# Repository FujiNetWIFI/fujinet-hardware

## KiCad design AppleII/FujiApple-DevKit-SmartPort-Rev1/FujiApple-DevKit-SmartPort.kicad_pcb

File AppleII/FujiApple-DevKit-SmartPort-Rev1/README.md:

Interactive BOM - https://djtersteegc.github.io/fujinet-hardware/AppleII/ibom-DevKit-SmartPort-v1.0.html

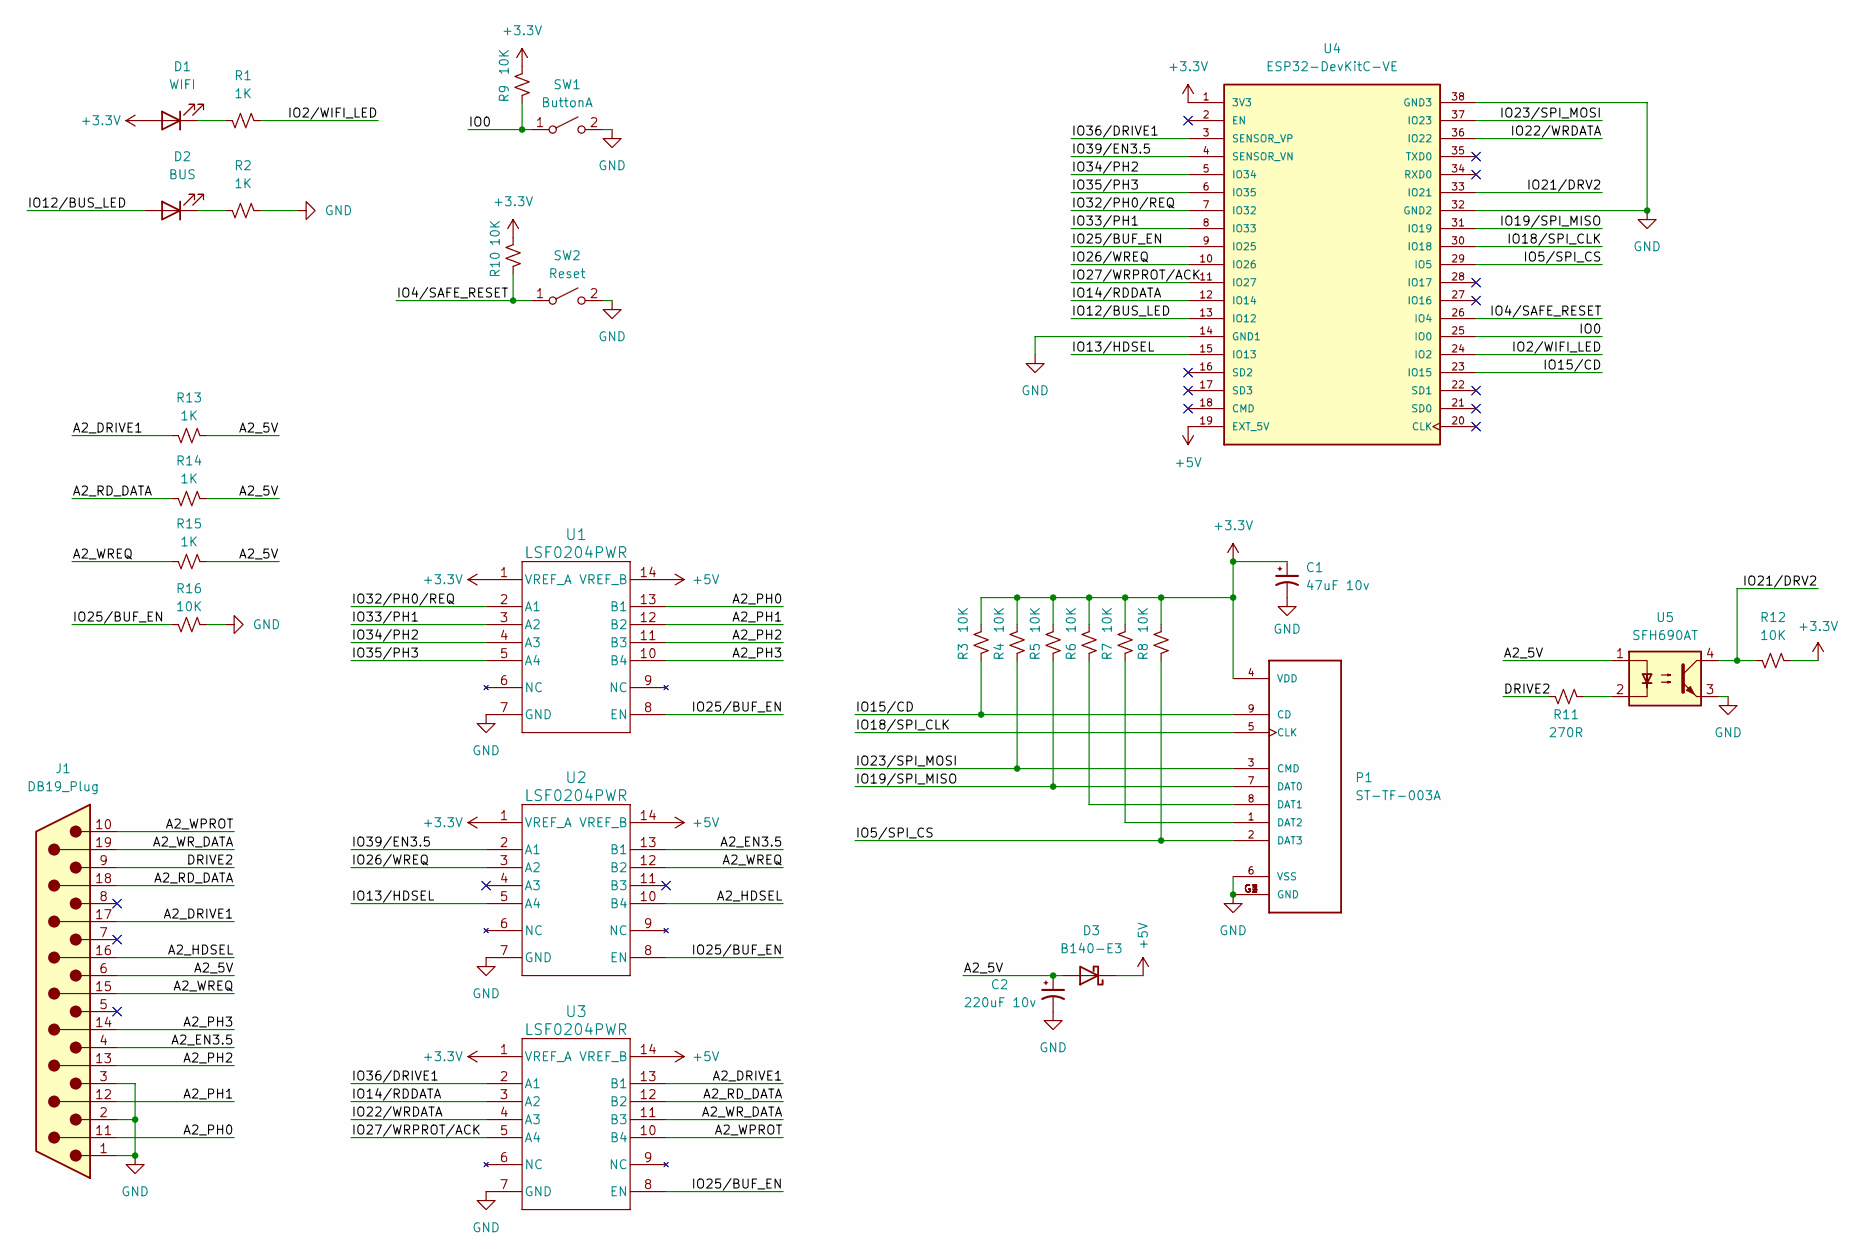
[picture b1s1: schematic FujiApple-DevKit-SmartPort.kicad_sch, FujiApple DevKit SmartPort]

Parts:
C1: 47uF 10v; CP_EIA-3528-15_AVX-H_Pad1.50x2.35mm_HandSolder
C2: 220uF 10v; CP_EIA-7343-30_AVX-N_Pad2.25x2.55mm_HandSolder
D1: WIFI; 1204 Side Emitting LED
D2: BUS; 1204 Side Emitting LED
D3: B140-E3; D_SMA
J1: DB19_Plug; DSUB-19_Male_Vertical_P2.77x2.84mm_Narrow_MountingHoles_Ful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
P1: ST-TF-003A; SUNTECH_ST-TF-003A
R1, R2, R13, R14, R15: 1K; R_0805_2012Metric_Pad1.20x1.40mm_HandSolder
R3, R4, R5, R6, R7, R8, R9, R10, R12, R16: 10K; R_0805_2012Metric_Pad1.20x1.40mm_HandSolder
R11: 270R; R_0805_2012Metric_Pad1.20x1.40mm_HandSolder
SW1: ButtonA; SW_Push_SPST_NO_Alps_SKRK
SW2: Reset; SW_Push_SPST_NO_Alps_SKRK
U1, U2, U3: LSF0204PWR; TSSOP-14_4.4x5mm_P0.65mm
U4: ESP32-DevKitC-VE; MODULE_ESP32-DEVKITC-32U; PARTREV N/A
U5: SFH690AT; SO-4_4.4x3.9mm_P2.54mm

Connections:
+3.3V: C1.1, D1.2 (A), P1.4 (VDD), R3.2, R4.2, R5.2, R6.2, R7.2, R8.2, R9.2, R10.2, R12.2, U1.1 (VREF_A), U2.1 (VREF_A), U3.1 (VREF_A), U4.1 (3V3)
+5V: D3.1 (K), U1.14 (VREF_B), U2.14 (VREF_B), U3.14 (VREF_B), U4.19 (EXT_5V)
/A2_5V: C2.1, D3.2 (A), J1.6, R13.2, R14.2, R15.2, U5.1
/A2_DRIVE1: J1.17, R13.1, U3.13 (B1)
/A2_EN3.5: J1.4, U2.13 (B1)
/A2_HDSEL: J1.16, U2.10 (B4)
/A2_PH0: J1.11, U1.13 (B1)
/A2_PH1: J1.12, U1.12 (B2)
/A2_PH2: J1.13, U1.11 (B3)
/A2_PH3: J1.14, U1.10 (B4)
/A2_RD_DATA: J1.18, R14.1, U3.12 (B2)
/A2_WPROT: J1.10, U3.10 (B4)
/A2_WREQ: J1.15, R15.1, U2.12 (B2)
/A2_WR_DATA: J1.19, U3.11 (B3)
/DRIVE2: J1.9, R11.1
/IO0: R9.1, SW1.1 (A), U4.25 (IO0)
/IO2/WIFI_LED: R1.2, U4.24 (IO2)
/IO4/SAFE_RESET: R10.1, SW2.1 (A), U4.26 (IO4)
/IO5/SPI_CS: P1.2 (DAT3), R8.1, U4.29 (IO5)
/IO12/BUS_LED: D2.2 (A), U4.13 (IO12)
/IO13/HDSEL: U2.5 (A4), U4.15 (IO13)
/IO14/RDDATA: U3.3 (A2), U4.12 (IO14)
/IO15/CD: P1.9 (CD), R3.1, U4.23 (IO15)
/IO18/SPI_CLK: P1.5 (CLK), U4.30 (IO18)
/IO19/SPI_MISO: P1.7 (DAT0), R5.1, U4.31 (IO19)
/IO21/DRV2: R12.1, U4.33 (IO21), U5.4
/IO22/WRDATA: U3.4 (A3), U4.36 (IO22)
/IO23/SPI_MOSI: P1.3 (CMD), R4.1, U4.37 (IO23)
/IO25/BUF_EN: R16.1, U1.8 (EN), U2.8 (EN), U3.8 (EN), U4.9 (IO25)
/IO26/WREQ: U2.3 (A2), U4.10 (IO26)
/IO27/WRPROT/ACK: U3.5 (A4), U4.11 (IO27)
/IO32/PH0/REQ: U1.2 (A1), U4.7 (IO32)
/IO33/PH1: U1.3 (A2), U4.8 (IO33)
/IO34/PH2: U1.4 (A3), U4.5 (IO34)
/IO35/PH3: U1.5 (A4), U4.6 (IO35)
/IO36/DRIVE1: U3.2 (A1), U4.3 (SENSOR_VP)
/IO39/EN3.5: U2.2 (A1), U4.4 (SENSOR_VN)
GND: C1.2, C2.2, J1.1, J1.2, J1.3, P1.6 (VSS), P1.G1 (GND), P1.G2 (GND), P1.G3 (GND), P1.G4 (GND), R2.2, R16.2, SW1.2 (B), SW2.2 (B), U1.7 (GND), U2.7 (GND), U3.7 (GND), U4.14 (GND1), U4.32 (GND2), U4.38 (GND3), U5.3
unnamed: D1.1 (K), R1.1
unnamed: D2.1 (K), R2.1
unnamed: P1.8 (DAT1), R6.1
unnamed: P1.1 (DAT2), R7.1
unnamed: R11.2, U5.2

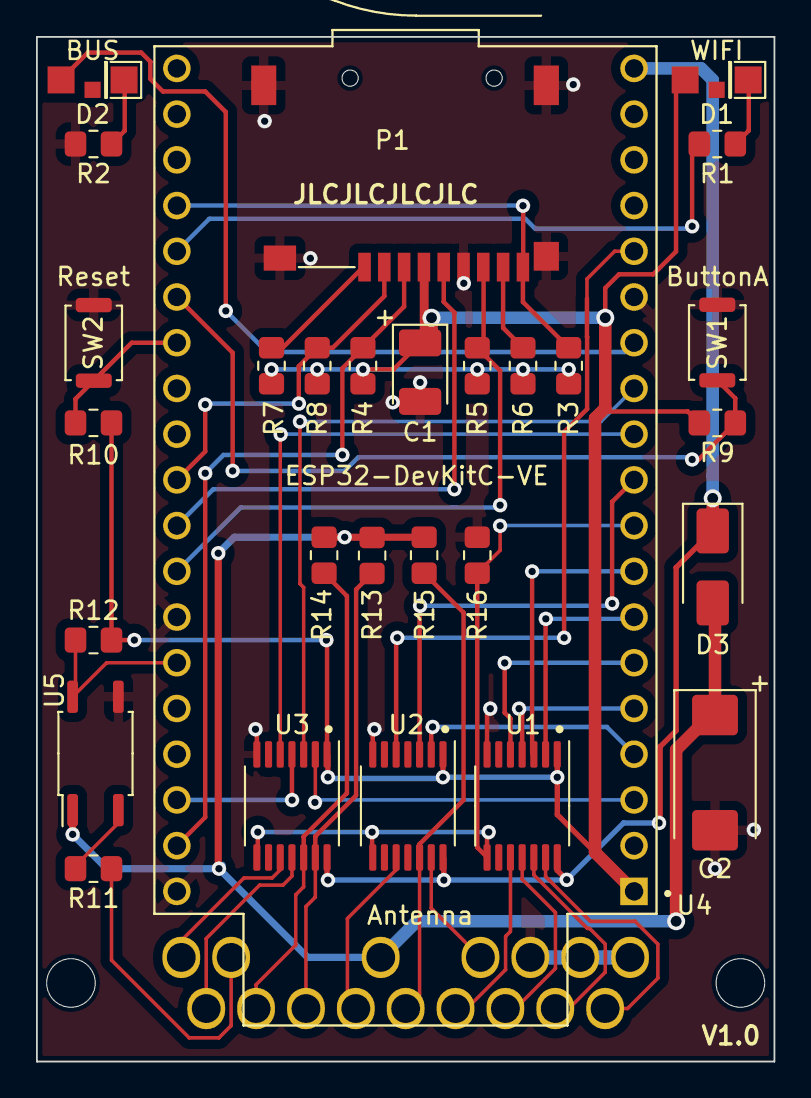
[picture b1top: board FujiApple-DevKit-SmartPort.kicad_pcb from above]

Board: 2 copper layers, 41.0 x 56.9 mm, 30 parts (1 on the bottom side), 43 nets.

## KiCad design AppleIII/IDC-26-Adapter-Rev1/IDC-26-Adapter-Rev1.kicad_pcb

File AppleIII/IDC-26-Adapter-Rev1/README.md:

An IDC-26  to IDC-20 adapter allowing to to use yourApple II Fujinet, Floppy Emu, or Disk II drive on the external floppy port of an Apple III.  Based on the work of [ThorstenBr](https://github.com/ThorstenBr/AppleIII_diskII), but redesigned to plug directly into the external port and adds the option to route the drive 2 enable signal to pin 17, since Fujinet uses a different pin than the Floppy Emu which expects that signal on pin 5.

[Schematic](https://djtersteegc.github.io/fujinet-hardware/AppleIII/Schematic-IDC-26-Adapter-Rev1.pdf)

# BOM

[Interactive BOM](https://djtersteegc.github.io/fujinet-hardware/AppleIII/ibom-Rev1.html)

| Component                          | Qty  | Notes                                 | LCSC                                                         |
| ---------------------------------- | ---- | ------------------------------------- | ------------------------------------------------------------ |
| IDC-20 2.54mm 2x10 Male Box Header | 1    |                                       | [C429961](https://www.lcsc.com/product-detail/IDC-Connectors_JILN-321020SG0ABK00A01_C429961.html) |
| IDC-26 2.54mm 2x13 Female Header   | 1    | Try to find one with a key            | [C2834333](https://www.lcsc.com/product-detail/Female-Headers_TXGA-FFH25407-D26S1004K6K_C2834333.html) |
| 74LS32 SOP or SOIC                 | 1    | SOIC-14_3.9x8.7mm_P1.27mm             | [C521171](https://www.lcsc.com/product-detail/Logic-Gates_XINLUDA-XL74LS32_C521171.html) |
| 470R 0805 Resistor                 | 1    | Only needed for Floppy Emu mode build | [C17710](https://www.lcsc.com/product-detail/Chip-Resistor-Surface-Mount_UNI-ROYAL-Uniroyal-Elec-0805W8F4700T5E_C17710.html) |
| 3.3K 0805 Resistor                 | 3    |                                       | [C26010](https://www.lcsc.com/product-detail/Chip-Resistor-Surface-Mount_UNI-ROYAL-Uniroyal-Elec-0805W8F3301T5E_C26010.html) |
| 100nf 0805 Capacitor               | 1    |                                       | [C28233](https://www.lcsc.com/product-detail/Multilayer-Ceramic-Capacitors-MLCC-SMD-SMT_Samsung-Electro-Mechanics-CL21B104KCFNNNE_C28233.html) |

# Case

The case parts are designed to printed at a 0.2mm layer height and snap together by inserting the wider tab first and then pushing down on the shorter tab side near the 72LS32 chip.  I found the tab on the lid broke off when using matte PLA with it's lower layer bond strength, but regular PLA or PLA+ (and probably PETG) worked fine and could be assembled and disassambled multiple times.  Your mileage may vary.

One issue observed with using a non-keyed female IDC-26 connector is the ability to misalign by one pin inside of the Apple III's IDC-26 male connector when inserting the adpater if you aren't careful. There is a "sleeve" that can be printed to press over the connector to prevent this misalignment from happening.  It's designed as a friction fit based on the generic Chinese connector I was using and a Bambu A1 printing PLA, so tolerances may need to be tweaked for your printer/connector combination.

# Solder Jumpers

**-12V** - Routes -12V to pin 9

**12V** - Routes +12V to pins 13 and 15.  Also pin 17 and 19 depending on their jumper positions.

**PIN5** - Routes either the Drive2 signal or GND to Pin 5.  For use with the Floppy Emu, do NOT also then route Drive2 to Pin17.

**PIN17** - Routes either the Drive 2 signal or +12V to Pin 17. For use with the Fujinet, do NOT also then route Drive2 to Pin5.

**Pin 19** - Routes either the Drive 3 signal or +12V to Pin 19. For use with the Fujinet, experimental, not currently supported in hardware or firmware.

Here's a table of the different ways to can build this and what works.  If you route either Drive2 or Drive3 to pin 17 and 19, you must **NEVER** then attempt to plug an actual Disk II drive into this since they internally bridge +12V on all four pins and will backfeed that voltage into your Apple III drive enable lines.

| Mode       | -12V    | 12V     | Pin 5 | Pin 17 | Pin 19 |
| ---------- | ------- | ------- | ----- | ------ | ------ |
| Disk II    | Closed  | Closed  | GND   | +12V   | +12V   |
| Fujinet    | Open    | Open    | GND   | DRV2   | DRV3   |
| Floppy Emu | Closed* | Closed* | DRV2  | +12V*  | +12V*  |

| Mode       | Disk II                | Fujinet                   | Floppy Emu                |
| ---------- | ---------------------- | ------------------------- | ------------------------- |
| Disk II    | Yes                    | Drive 1 (as .d2) only     | Drive 1 (as .d2) only     |
| Fujinet    | **DANGER, DO NOT USE** | Drive 1 (.d2) and 2 (.d3) | Drive 1 (as .d2) only     |
| Floppy Emu | Yes                    | Drive 1 (as .d2) only     | Drive 1 (.d2) and 2 (.d3) |

*If you don't plan on using a Disk II, I would recommend NOT closing any of the 12V jumpers for safety's sake, since these voltages are not needed by any of these modern drive emulators.

# Assembly

Assemble the SMD components and solder the jumpers as needed.  Note that the 74LS32 chip mounts upside down with pin 1 on the lower right. Then solder on the two IDC connectors, make sure to pay attention to which side of the board they go on.

I like to then add a label printed on a P-touch (0.23mm black on transparent tape) to denote the mode the adapter was built for.

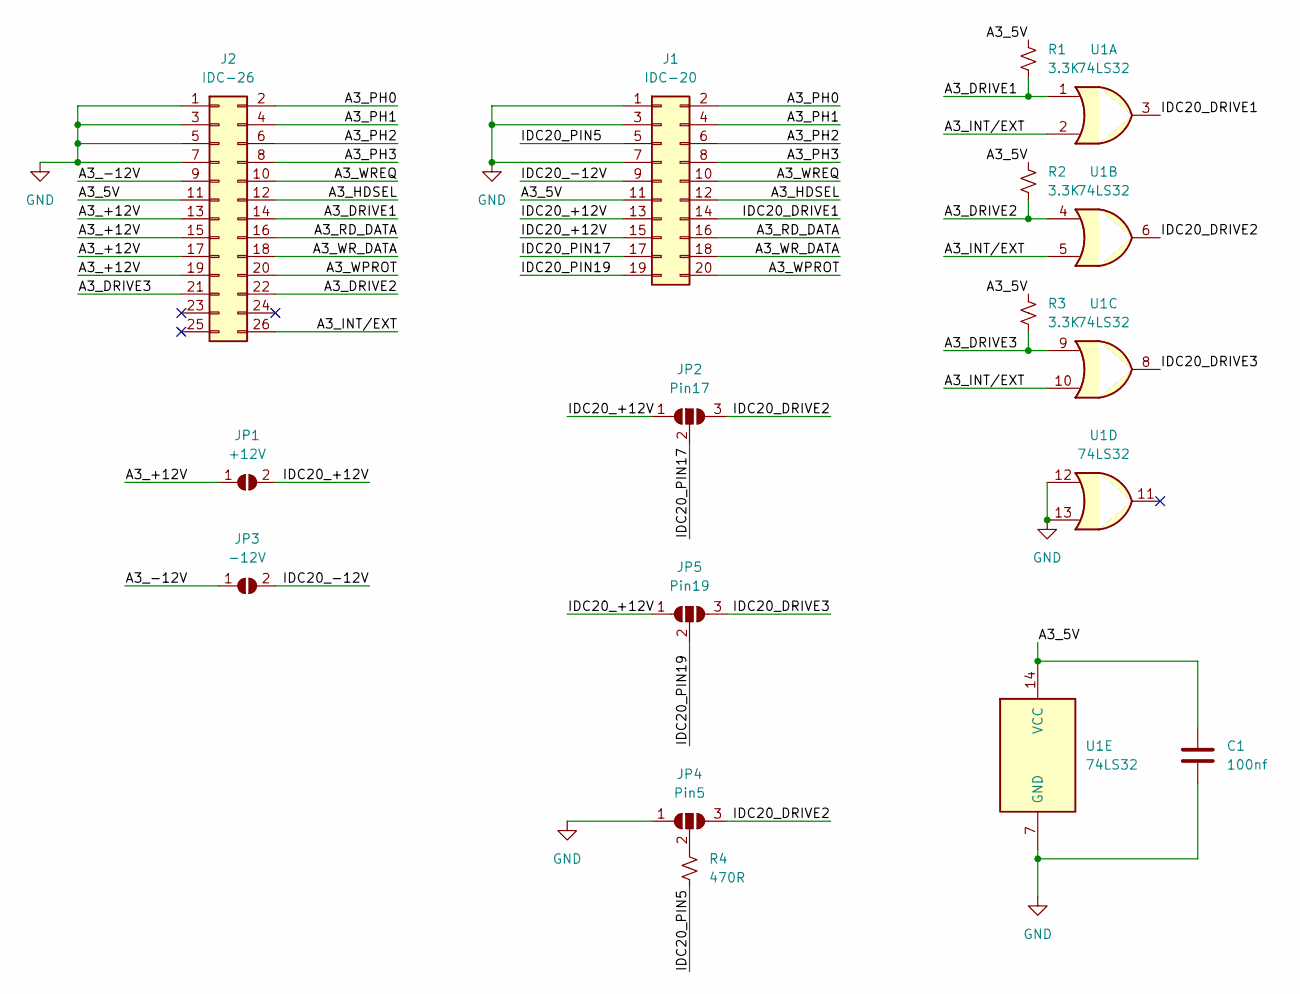
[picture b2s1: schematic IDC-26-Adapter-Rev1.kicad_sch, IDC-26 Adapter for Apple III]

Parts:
C1: 100nf; C_0805_2012Metric_Pad1.18x1.45mm_HandSolder
J1: IDC-20; IDC-Header_2x10_P2.54mm_Vertical
J2: IDC-26; PinSocket_2x13_P2.54mm_Vertical
JP1: +12V; SolderJumper-2_P1.3mm_Open_RoundedPad1.0x1.5mm
JP2: Pin17; SolderJumper-3_P1.3mm_Open_RoundedPad1.0x1.5mm_NumberLabels
JP3: -12V; SolderJumper-2_P1.3mm_Open_RoundedPad1.0x1.5mm
JP4: Pin5; SolderJumper-3_P1.3mm_Open_RoundedPad1.0x1.5mm_NumberLabels
JP5: Pin19; SolderJumper-3_P1.3mm_Open_RoundedPad1.0x1.5mm_NumberLabels
R1, R2, R3: 3.3K; R_0805_2012Metric_Pad1.20x1.40mm_HandSolder
R4: 470R; R_0805_2012Metric_Pad1.20x1.40mm_HandSolder
U1: 74LS32; SOIC-14_3.9x8.7mm_P1.27mm

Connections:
/A3_5V: C1.1, J1.11, J2.11, R1.1, R2.1, R3.1, U1.14 (VCC)
/A3_+12V: J2.13, J2.15, J2.17, J2.19, JP1.1 (A)
/A3_-12V: J2.9, JP3.1 (A)
/A3_DRIVE1: J2.14, R1.2, U1.1
/A3_DRIVE2: J2.22, R2.2, U1.4
/A3_DRIVE3: J2.21, R3.2, U1.9
/A3_HDSEL: J1.12, J2.12
/A3_INT/EXT: J2.26, U1.2, U1.5, U1.10
/A3_PH0: J1.2, J2.2
/A3_PH1: J1.4, J2.4
/A3_PH2: J1.6, J2.6
/A3_PH3: J1.8, J2.8
/A3_RD_DATA: J1.16, J2.16
/A3_WPROT: J1.20, J2.20
/A3_WREQ: J1.10, J2.10
/A3_WR_DATA: J1.18, J2.18
/IDC20_+12V: J1.13, J1.15, JP1.2 (B), JP2.1 (A), JP5.1 (A)
/IDC20_-12V: J1.9, JP3.2 (B)
/IDC20_DRIVE1: J1.14, U1.3
/IDC20_DRIVE2: JP2.3 (B), JP4.3 (B), U1.6
/IDC20_DRIVE3: JP5.3 (B), U1.8
/IDC20_PIN5: J1.5, R4.2
/IDC20_PIN17: J1.17, JP2.2 (C)
/IDC20_PIN19: J1.19, JP5.2 (C)
GND: C1.2, J1.1, J1.3, J1.7, J2.1, J2.3, J2.5, J2.7, JP4.1 (A), U1.7 (GND), U1.12, U1.13
unnamed: JP4.2 (C), R4.1

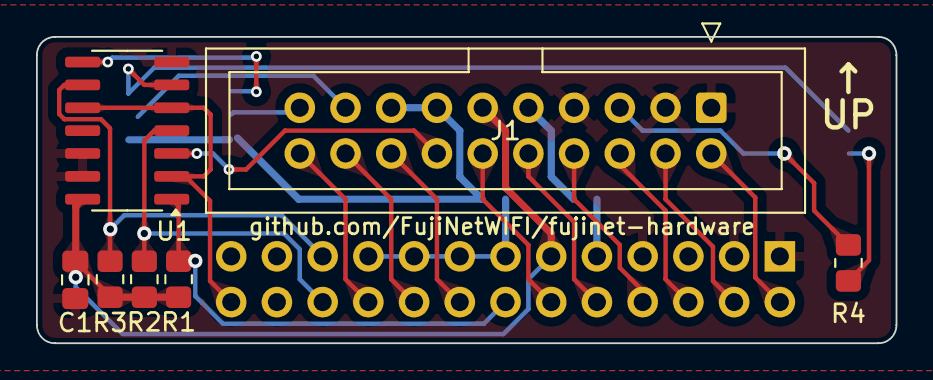
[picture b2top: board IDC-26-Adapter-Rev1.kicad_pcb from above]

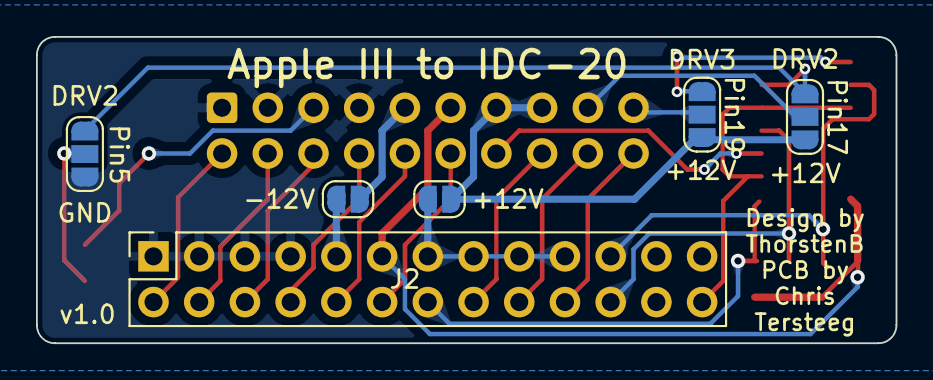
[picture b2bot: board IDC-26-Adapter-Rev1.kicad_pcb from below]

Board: 2 copper layers, 47.8 x 17.0 mm, 13 parts (6 on the bottom side), 26 nets.

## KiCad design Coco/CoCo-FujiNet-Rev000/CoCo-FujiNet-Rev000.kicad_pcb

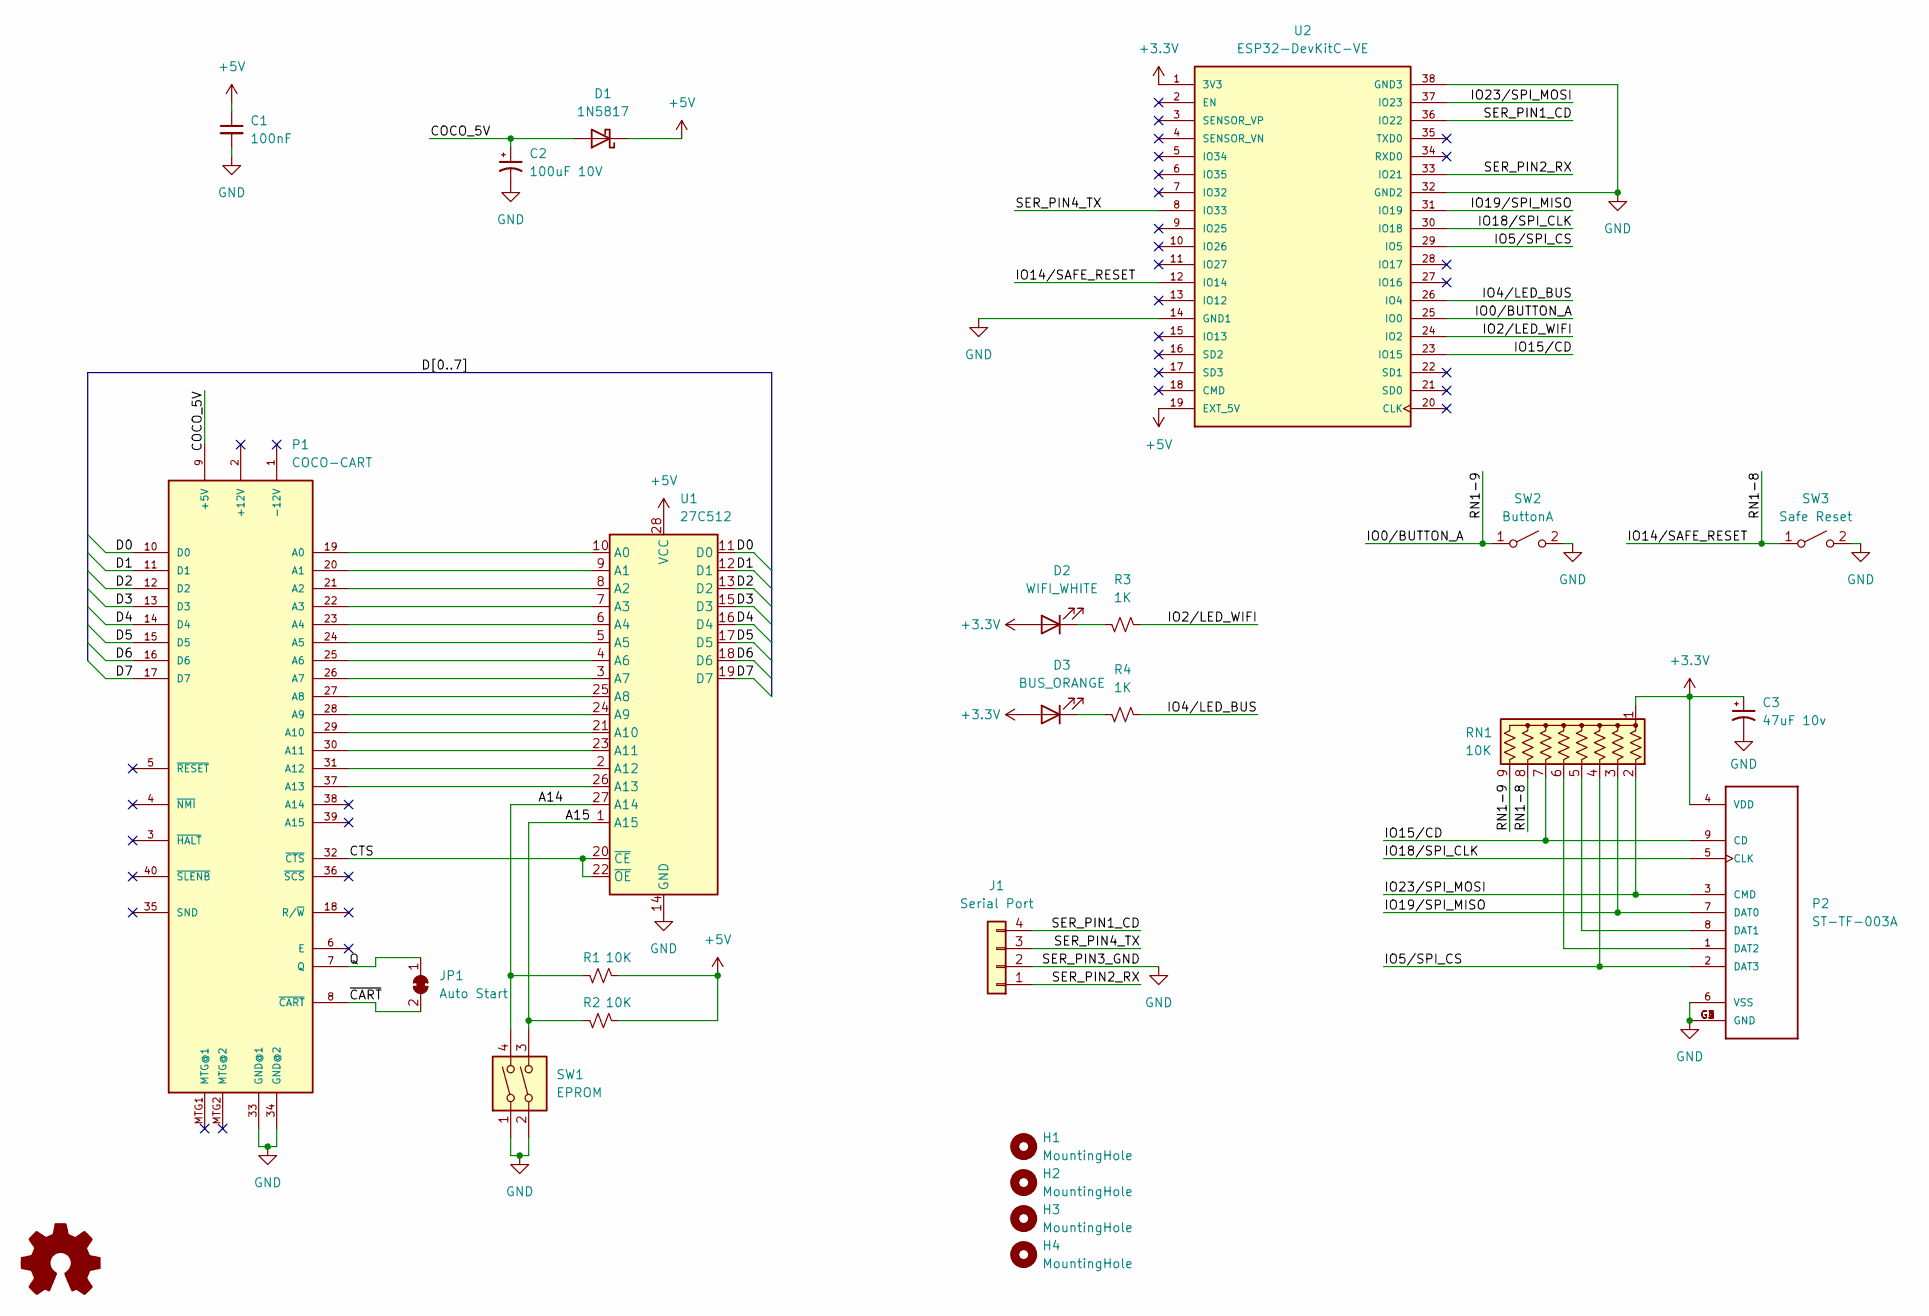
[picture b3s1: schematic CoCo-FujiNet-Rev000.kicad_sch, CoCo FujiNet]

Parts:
C1: 100nF; C_Disc_D4.7mm_W2.5mm_P5.00mm
C2: 100uF 10V; CP_Radial_D6.3mm_P2.50mm
C3: 47uF 10v; CP_EIA-3528-15_AVX-H_Pad1.50x2.35mm_HandSolder
D1: 1N5817; D_DO-41_SOD81_P10.16mm_Horizontal
D2: WIFI_WHITE; LED_D3.0mm
D3: BUS_ORANGE; LED_D3.0mm
H1, H2, H3, H4: MountingHole; MountingHole_3.2mm_M3
J1: Serial Port; PinHeader_1x04_P2.54mm_Vertical
JP1: Auto Start; SolderJumper-2_P1.3mm_Bridged_RoundedPad1.0x1.5mm
P1: COCO-CART
P2: ST-TF-003A; SUNTECH_ST-TF-003A
R1, R2: 10K; R_Axial_DIN0207_L6.3mm_D2.5mm_P7.62mm_Horizontal
R3, R4: 1K; R_Axial_DIN0207_L6.3mm_D2.5mm_P7.62mm_Horizontal
RN1: 10K; R_Array_SIP9
SW1: EPROM; SW_DIP_SPSTx02_Slide_9.78x7.26mm_W7.62mm_P2.54mm
SW2: ButtonA; SW_Tactile_SPST_Angled_PTS645Vx58-2LFS
SW3: Safe Reset; SW_Tactile_SPST_Angled_PTS645Vx58-2LFS
U1: 27C512; DIP-28_W15.24mm
U2: ESP32-DevKitC-VE; MODULE_ESP32-DEVKITC-32U; PARTREV N/A

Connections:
+3.3V: C3.1, D2.2 (A), D3.2 (A), P2.4 (VDD), RN1.1 (common), U2.1 (3V3)
+5V: C1.1, D1.1 (K), R1.2, R2.2, U1.28 (VCC), U2.19 (EXT_5V)
/A14: R1.1, SW1.4, U1.27 (A14)
/A15: R2.1, SW1.3, U1.1 (A15)
/COCO_5V: C2.1, D1.2 (A), P1.9 (+5V)
/CTS: P1.32 (~CTS), U1.20 (~CE), U1.22 (~OE)
/D0: P1.10 (D0), U1.11 (D0)
/D1: P1.11 (D1), U1.12 (D1)
/D2: P1.12 (D2), U1.13 (D2)
/D3: P1.13 (D3), U1.15 (D3)
/D4: P1.14 (D4), U1.16 (D4)
/D5: P1.15 (D5), U1.17 (D5)
/D6: P1.16 (D6), U1.18 (D6)
/D7: P1.17 (D7), U1.19 (D7)
/IO0/BUTTON_A: RN1.9 (R8), SW2.1 (A), U2.25 (IO0)
/IO2/LED_WIFI: R3.2, U2.24 (IO2)
/IO4/LED_BUS: R4.2, U2.26 (IO4)
/IO5/SPI_CS: P2.2 (DAT3), RN1.4 (R3), U2.29 (IO5)
/IO14/SAFE_RESET: RN1.8 (R7), SW3.1 (A), U2.12 (IO14)
/IO15/CD: P2.9 (CD), RN1.7 (R6), U2.23 (IO15)
/IO18/SPI_CLK: P2.5 (CLK), U2.30 (IO18)
/IO19/SPI_MISO: P2.7 (DAT0), RN1.3 (R2), U2.31 (IO19)
/IO23/SPI_MOSI: P2.3 (CMD), RN1.2 (R1), U2.37 (IO23)
/Q: JP1.1 (A), P1.7 (Q)
/SER_PIN1_CD: J1.4, U2.36 (IO22)
/SER_PIN2_RX: J1.1, U2.33 (IO21)
/SER_PIN4_TX: J1.3, U2.8 (IO33)
/~CART: JP1.2 (B), P1.8 (~CART)
GND: C1.2, C2.2, C3.2, J1.2, P1.33 (GND@1), P1.34 (GND@2), P2.6 (VSS), P2.G1 (GND), P2.G2 (GND), P2.G3 (GND), P2.G4 (GND), SW1.1, SW1.2, SW2.2 (B), SW3.2 (B), U1.14 (GND), U2.14 (GND1), U2.32 (GND2), U2.38 (GND3)
unnamed: D2.1 (K), R3.1
unnamed: D3.1 (K), R4.1
unnamed: P1.19 (A0), U1.10 (A0)
unnamed: P1.20 (A1), U1.9 (A1)
unnamed: P1.21 (A2), U1.8 (A2)
unnamed: P1.22 (A3), U1.7 (A3)
unnamed: P1.23 (A4), U1.6 (A4)
unnamed: P1.24 (A5), U1.5 (A5)
unnamed: P1.25 (A6), U1.4 (A6)
unnamed: P1.26 (A7), U1.3 (A7)
unnamed: P1.27 (A8), U1.25 (A8)
unnamed: P1.28 (A9), U1.24 (A9)
unnamed: P1.29 (A10), U1.21 (A10)
unnamed: P1.30 (A11), U1.23 (A11)
unnamed: P1.31 (A12), U1.2 (A12)
unnamed: P1.37 (A13), U1.26 (A13)
unnamed: P2.8 (DAT1), RN1.5 (R4)
unnamed: P2.1 (DAT2), RN1.6 (R5)

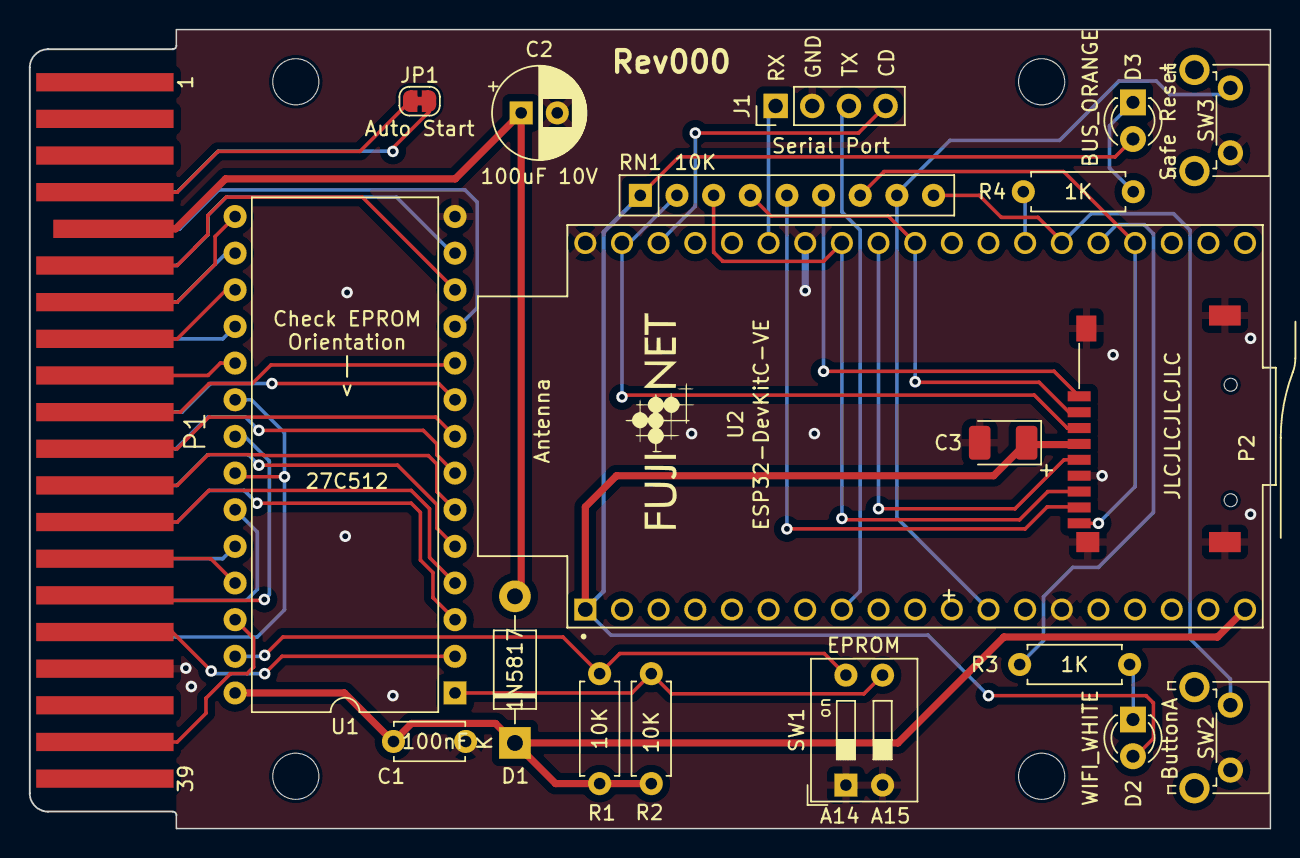
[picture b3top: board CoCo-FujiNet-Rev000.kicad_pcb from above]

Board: 2 copper layers, 86.0 x 55.4 mm, 24 parts (0 on the bottom side), 47 nets.

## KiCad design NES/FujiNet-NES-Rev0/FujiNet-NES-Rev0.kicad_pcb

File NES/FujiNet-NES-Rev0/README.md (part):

# FujiNet-NES Rev0

All-in-one **NES FujiNet cartridge**: one board in a 72-pin Game Pak shell
carrying both halves of the FujiNet stack.

- **RP2354B** (RP2350B die + 2 MB flash, QFN-80, all 48 GPIO used) runs the
  `fujines` cart firmware from `fujinet-firmware/pico/nes` (branch
  `nes-bringup`). It sits on the 5 V cart bus directly through its
  5 V-tolerant pads, serves `$5000-$7FFF` (mailbox, loader ROM, WRAM) and the
  power-on reset vectors itself, watches every CPU write for mapper
  registers, and drives the two SRAMs' bank lines from PIO lookup tables.
- **2x AS6C4008-55** (512K x 8, TSOP-I-32) are the PRG and CHR memories the
  console addresses itself, on the 5 V rail so their outputs drive the 5 V bus.
- **74HCT595 / 253 / 14 / 20 / 00 / 32** on 5 V: the slow control bits, the
  CIRAM A10 mirroring mux, the console-power gate and the SRAM strobe decode.
- **ESP32-S3-WROOM-1-N16R8** runs the **`fujiversal-nes`** build of
  fujinet-firmware and is the USB *host* of the RP (CDC, VID 0xCafe) on
  IO19/IO20; it re-flashes the RP over PICOBOOT.
- **USB-C** (power + CP2102N UART with UMH3N auto-program), **microSD**
  (SPI on IO38-41, card-detect IO42), **WS2812B-2020** status LED,
  RESET / BOOTSEL / S3 EN / S3 BOOT buttons.
- **CIClone** footprint (ATtiny13A, DNP) on the four CIC fingers, so a stock
  NES-001 can run the cart once lockout firmware exists.

**Status (2026-10-01):** schematic audited against the manufacturer
datasheets and redone (`docs/design-review-rev0.md`); 6-layer 1.2 mm layout
generated on the measured NES-EWROM-01 outline -- see *Status* below for
the routing / DRC / export state. **No board has been built**, nothing has
run on a console.

## Edge connector

72 pins, **2.50 mm pitch** (not 0.1 in), pins 1-36 on the label side of the
board, 37-72 on the back, pin N over pin N+36 (nesdev wiki, *Cartridge
connector*). Looking at the label side with the fingers down, the fingers
read **36 .. 1 from left to right: pin 1 is at the right.** The project
footprint `NES_Cart_Edge_72` follows the NES-EWROM-01 board measured on the
nesdev *NES cartridge dimensions* page: fingers 2.0 x 12.0 mm (the four end
fingers 3.0 mm wide at +/-44.25 mm), copper 1.0-13.0 mm in from the bevelled
edge, one solder-mask window per face (the lower 6.5 mm on the label side,
11 mm on the back) exactly as Nintendo's boards have. `tools/check_nets.py`
asserts the orientation from the footprint file and
`tools/audit/edge_orientation.py` compares it with the reference pads.

| Pin | Signal | Net | Pin | Signal | Net |
|---|---|---|---|---|---|
| 1 | GND | GND | 37 | SYSTEM CLK | nc |
| 2-13 | CPU A11..A0 | CA11..CA0 | 38 | M2 | M2 |
| 14 | CPU R/W | RW | 39-41 | CPU A12, A13, A14 | CA12-14 |
| 15 | /IRQ | IRQ_N | 42-49 | CPU D7..D0 | CD7..CD0 |
| 16-20 | EXP0-4 | nc | 50 | /ROMSEL | ROMSEL_N |
| 21 | PPU /RD | PPU_RD_N | 51-55 | EXP9-5 | nc |
| 22 | CIRAM A10 | CIRAM_A10 | 56 | PPU /WR | PPU_WR_N |
| 23-29 | PPU A6..A0 | PA6..PA0 | 57 | CIRAM /CE | CIRAM_CE_N |
| 30-33 | PPU D0-D3 | PD0-3 | 58 | PPU /A13 | PA13_N |
| 34, 35 | CIC toPak, toMB | CIC_TOPAK, CIC_TOMB | 59-61 | PPU A7, A8, A9 | PA7-9 |
| 36 | +5V | CONS_5V | 62, 63 | PPU A11, **A10** | PA11, PA10 |
| | | | 64, 65 | PPU A12, A13 | PA12, PA13 |
| | | | 66-69 | PPU D7..D4 | PD7..PD4 |
| | | | 70, 71 | CIC +RST, CLK | CIC_RST, CIC_CLK |
| | | | 72 | GND | GND |

EXP0-9 and SYSTEM CLK are open. **/IRQ has no pull-up on the cart**: the
console has a 10k pull-up (nesdev), the firmware drives the line low or
releases it.

## RP2354B pin map

Exactly `nes_cart.h`; `tools/check_nets.py` reads the header and checks the
netlist against it (453 checks, including the decode gate by gate).

| GPIO | Net | Goes to |
|---|---|---|
| 0-12 | CA0-CA12 | edge CPU A0-A12 and PRG SRAM A0-A12 |
| 13-20 | CD0-CD7 | edge CPU D0-D7 and PRG SRAM DQ0-7 |
| 21 | M2 | edge 38, the '20 (PRG /WE), test pad |
| 22 | RW | edge 14, '14 and '00 inputs |
| 23 | ROMSEL_N | edge 50, '14 input |
| 24, 25 | CA13, CA14 | edge 40, 41 (PIO1's PRG index) |
| 26-28 | PA10, PA11, PA12 | edge 63, 62, 64 (PIO0's CHR index); PA10/PA11 also '253 1I0/1I1 |
| 29, 30, 31 | SR_SER, SR_SCK, SR_RCK | 74HCT595 DS, SHCP, STCP |
| 32 | IRQ_N | edge 15, direct |
| 33-38 | PRG_A13-PRG_A18 | PRG SRAM A13-A18 (PIO1 table) |
| 39-47 | CHR_A10-CHR_A18 | CHR SRAM A10-A18 (PIO0 table) |

QFN-80 pin numbers were read against the RP2350 datasheet's pinout figure
and KiCad's `MCU_RaspberryPi:RP2354B` symbol; `gen_sch.py` refuses to write
a sheet if `design.py`'s table disagrees with the symbol.

'595 bits, Q0 first: `SRAM_EN`, `PRG_WE_EN`, `CHR_WE_EN`, `MIR0`, `MIR1`,
`FOURSCREEN`, `LED` (1k, green 0603), `SR_SPARE` (test pad). Every bit has a
100k pull-down and the register's **/OE is gated**: outputs float (so the
bits read 0) for ~70-170 ms after the 5 V rail comes up and whenever the
console is off, so the undefined power-on contents of the '595 can never
enable an SRAM before the RP has loaded it.

## Decode

All 74HCT, on the +5V rail. `ROMSEL = !ROMSEL_N`, `RW_N = !RW`.

```
VSENSE        = CONS_5V * 100k/(22k+100k) = 0.82 x CONS_5V   (TI 74HCT14 VT+ reaches 0.70 x VCC)
PWR_OK_N      = !VSENSE          PWR_OK = !PWR_OK_N          both on the '14 (Schmitt)
POR           = !POR_RC          POR_RC: 1 uF to +5V, 100k to GND (starts high, decays)
'595 /OE      = NAND(PWR_OK, POR)
PRG /CE       = NAND(ROMSEL, SRAM_EN)                       '20 (4-input, spare inputs high)
PRG /OE       = NAND(R/W, PWR_OK)                           '00
PRG /WE       = NAND(M2, ROMSEL, RW_N, PRG_WE_EN)            '20: one gate after M2 falls
CHR /CE       = PPU A13
CHR /OE       = PPU /RD | PWR_OK_N                          '32
CHR /WE       = PPU /WR | !CHR_WE_EN                        '32
CIRAM A10     = '253 half a { PPU A10, PPU A11, 0, 1 }[MIR1:MIR0], /OE = PWR_OK_N
CIRAM /CE     = '253 half b ( PPU /A13 | FOURSCREEN ), /OE = PWR_OK_N
```

Gate budget: '14 6 of 6, '20 2 of 2, '00 2 of 4, '32 3 of 4, '253 both
halves; every unused input is grounded. The truth table the firmware sees is
the one in `pico/nes/README.md`; the differences are in *how* the lines are
driven: `CIRAM /CE` tri-states with the console off instead of being a '32
output into a dead console, the PRG write strobe ends on M2 rather than on
the console's /ROMSEL decoder (`tools/audit/timing_margins.py`: 28 ns
worst-case after M2 falls against the 2A03's PROVISIONAL 30 ns data hold;
the first draft was 110 ns), and `FOURSCREEN` is a '595 bit with a pull-down.

### Timing budget (NTSC, nesdev and the AS6C4008-55 datasheet)

| Path | Budget | Spent |
|---|---|---|
| CPU read of PRG SRAM: /ROMSEL low to data valid | 330 ns | '14 + '20 (58 ns worst) + tACE 55 ns = 113 ns |
| CPU write to PRG SRAM (loader copy): data hold after /WE rises | tDH 0 ns | /WE rises <= 28 ns after M2 falls; 2A03 holds ~30 ns (PROVISIONAL) |
| write pulse / data setup | tWP 45 / tDW 25 ns | ~300 ns / ~228 ns |
| PPU fetch: PPU A10-A12 change to CHR data | 372 ns (2 dots) | PIO table ~45 ns + tACE 55 ns; /OE one '32 after /RD |
| Mirroring: PPU A10 to CIRAM A10 | same PPU access | '253 ~20 ns |
| CIRAM /CE from PPU /A13 | same | '32 + '253 ~40 ns |

## Power

- **Sources:** console +5V (edge 36, `CONS_5V`) through an **AO3401A
  P-FET** whose gate is VBUS: with no cable it is fully on (~24 mV at
  0.4 A), with USB present it is off and only its body diode remains,
  pointing into the cart, so USB never back-feeds the console. USB VBUS
  comes in through an SS34. Both meet on **+5V**. R22 (4.7k, VBUS to GND)
  holds the gate at 0 V with no cable: the SS34 is reverse-biased whenever
  the console powers the cart, and its leakage (0.5 mA max at 25 C) would
  otherwise lift the gate through the 69k sense divider alone and turn the
  FET off (added 2026-10-07, after layout; found by the SMS Rev0 audit).
- **+5V** feeds the two SRAMs, the six 74HCT packages (VCC minimum 4.5 V,
  which the Schottky drop of the first draft left no margin for), the
  WS2812B (datasheet VDD 3.7-5.3 V), the AP63203 buck and the AP2112K LDO.
- **+3V3** (AP63203, 2 A, 4 ms soft-start): ESP32-S3, microSD, CP2102N.
- **+3V3_RP** (AP2112K, 20 us start-up, ~60 mA): every RP2354B supply pin:
  IOVDD x8, QSPI_IOVDD, USB_OTP_VDD, ADC_AVDD, and the core-regulator input
  VREG_VIN with VREG_AVDD through 33R (the datasheet asks for those two to
  rise together). The RP2350's pads are 5 V-tolerant *only while IOVDD is
  powered*; on console-only power the buck's soft-start would leave them
  unpowered for ms with the 2A03's outputs already at 5 V. The LDO tracks the
  console rail as it rises instead. (Keeping VREG_VIN on the buck would also
  have left pin 64 boxed in between LX and FB with no via spot at 0.4 mm
  pitch; on the island it joins through a stub under the package.)
- **PWR_OK** is sensed on `CONS_5V`, before the FET, so a USB-powered cart in
  an unpowered console keeps both SRAM /OE high, the '595 off and the '253
  released. Because the SRAMs and logic stay on USB power, a loaded game
  survives a console power cycle while the cable is in.

## Flashing

- **ESP32-S3:** USB-C (CP2102N, esptool auto-program),
  `pio run -e fujiversal-nes -t upload`. The build embeds the RP image.
- **RP2354B:** flashed by the S3 over PICOBOOT at boot -- mailbox BOOTSEL
  doorbell first, else IO5 holds QSPI_SS low across an IO4 pulse on RUN
  (1k links, both 3.3 V, no transistors: `forceBootselViaPins()` drives
  low to assert). `fujiversal-nes.h` does not define `PIN_RP2040_RUN/BOOTSEL`
  yet; the board follows the IO4/IO5 contract and `check_nets.py` says so
  when it falls back to the INTV header.
- **Manual fallback:** hold SW2 (BOOTSEL) and press SW1 (RESET); in BOOTSEL
  the RP enumerates to the S3, not a PC.
- **Last resort:** test pads TP1 SWCLK, TP2 SWDIO, TP3 GND, TP4 RUN.
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
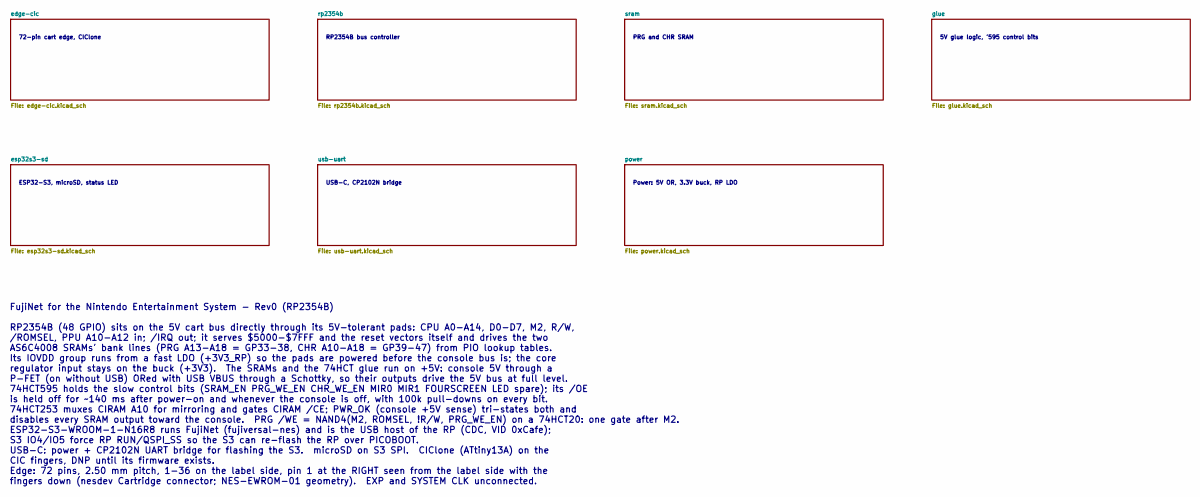
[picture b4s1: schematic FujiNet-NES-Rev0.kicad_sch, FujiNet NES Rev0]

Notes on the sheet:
72-pin cart edge, CIClone
RP2354B bus controller
PRG and CHR SRAM
5V glue logic, '595 control bits
ESP32-S3, microSD, status LED
USB-C, CP2102N bridge
Power: 5V OR, 3.3V buck, RP LDO
FujiNet for the Nintendo Entertainment System - Rev0 (RP2354B) RP2354B (48 GPIO) sits on the 5V cart bus directly through its 5V-tolerant pads: CPU A0-A14, D0-D7, M2, R/W, /ROMSEL, PPU A10-A12 in; /IRQ out; it serves $5000-$7FFF and the reset vectors itself and drives the two AS6C4008 SRAMs' bank l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

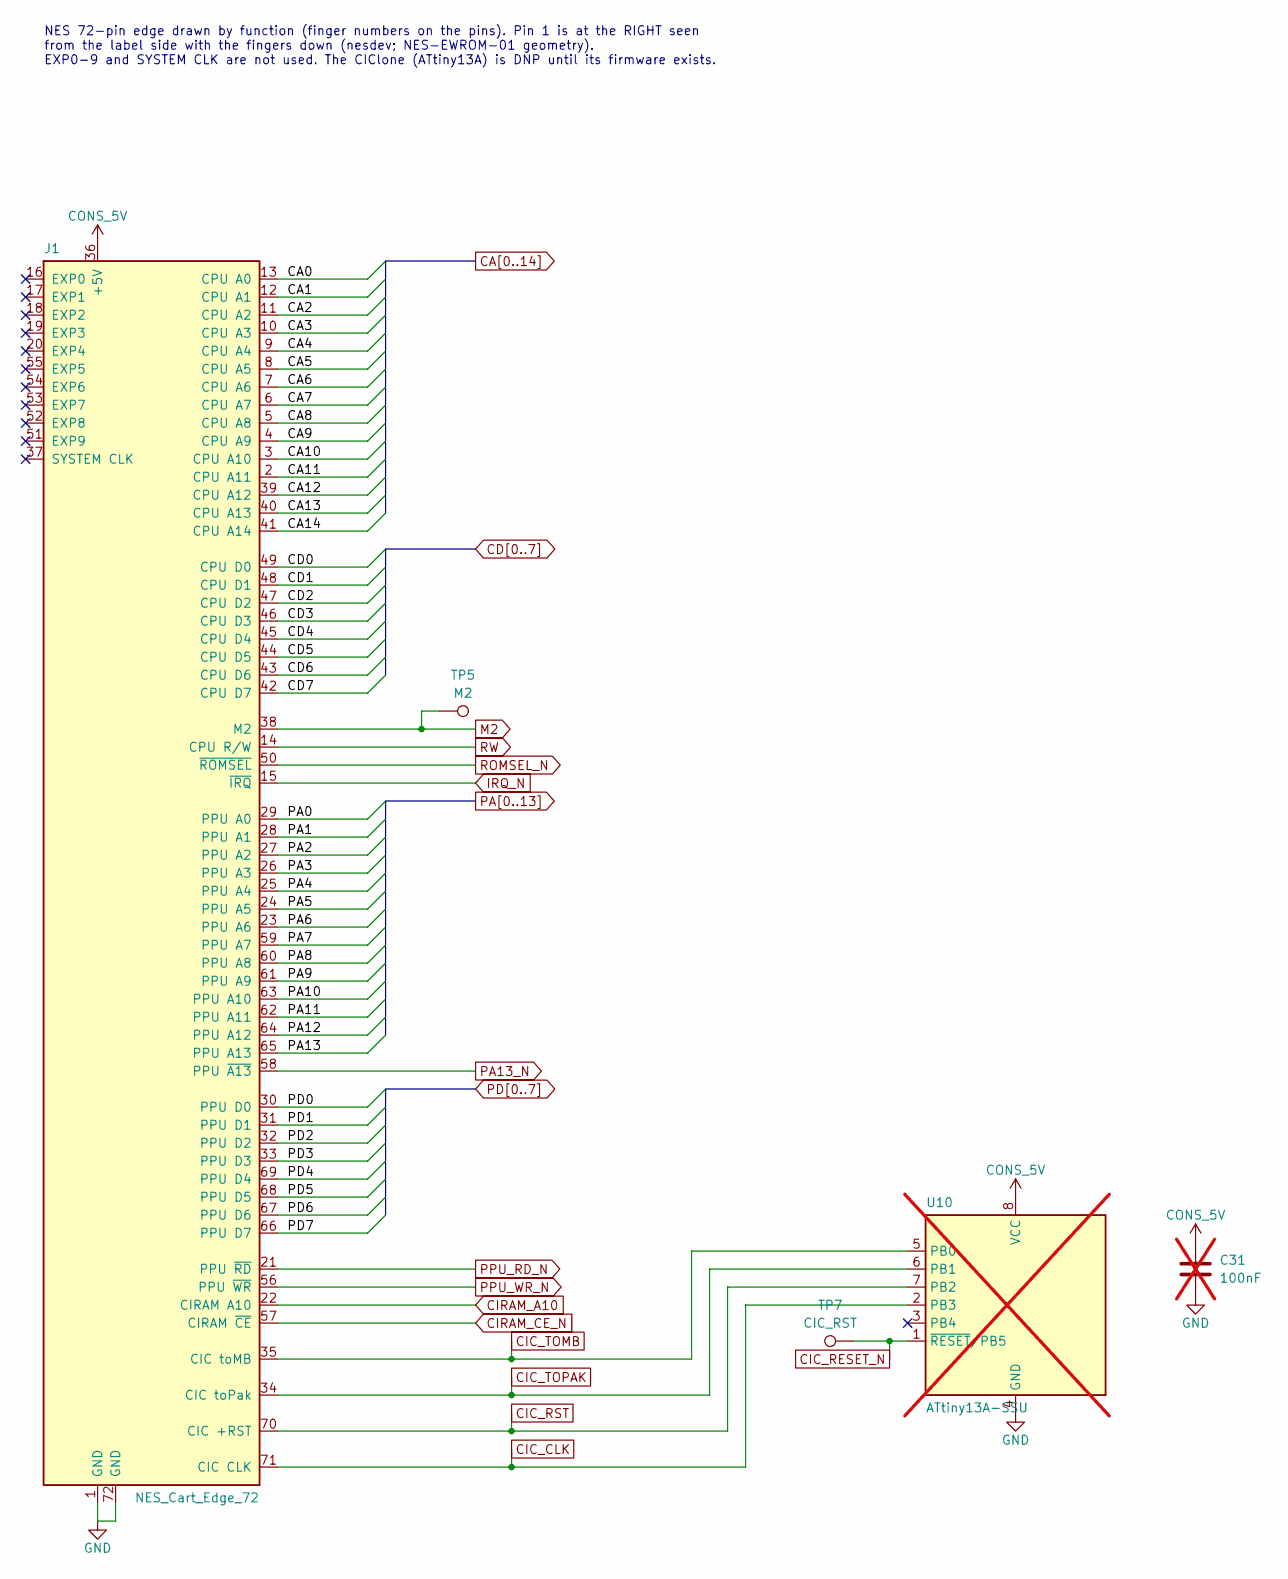
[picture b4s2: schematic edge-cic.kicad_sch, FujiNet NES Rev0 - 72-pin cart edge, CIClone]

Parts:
C31: 100nF; C_0603_1608Metric; MPN CC0603KRX7R9BB104; LCSC C14663; not fitted
J1: NES_Cart_Edge_72
TP5: M2; TestPoint_Pad_D1.5mm
TP7: CIC_RST; TestPoint_Pad_D1.5mm
U10: ATtiny13A-SSU; SOIC-8_3.9x4.9mm_P1.27mm; MPN ATTINY13A-SSUR; LCSC C40382; not fitted

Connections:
CA0: J1.13 (CPU A0); also elsewhere on the board
CA1: J1.12 (CPU A1); also elsewhere on the board
CA2: J1.11 (CPU A2); also elsewhere on the board
CA3: J1.10 (CPU A3); also elsewhere on the board
CA4: J1.9 (CPU A4); also elsewhere on the board
CA5: J1.8 (CPU A5); also elsewhere on the board
CA6: J1.7 (CPU A6); also elsewhere on the board
CA7: J1.6 (CPU A7); also elsewhere on the board
CA8: J1.5 (CPU A8); also elsewhere on the board
CA9: J1.4 (CPU A9); also elsewhere on the board
CA10: J1.3 (CPU A10); also elsewhere on the board
CA11: J1.2 (CPU A11); also elsewhere on the board
CA12: J1.39 (CPU A12); also elsewhere on the board
CA13: J1.40 (CPU A13); also elsewhere on the board
CA14: J1.41 (CPU A14); also elsewhere on the board
CD0: J1.49 (CPU D0); also elsewhere on the board
CD1: J1.48 (CPU D1); also elsewhere on the board
CD2: J1.47 (CPU D2); also elsewhere on the board
CD3: J1.46 (CPU D3); also elsewhere on the board
CD4: J1.45 (CPU D4); also elsewhere on the board
CD5: J1.44 (CPU D5); also elsewhere on the board
CD6: J1.43 (CPU D6); also elsewhere on the board
CD7: J1.42 (CPU D7); also elsewhere on the board
CIC_CLK: J1.71 (CIC CLK), U10.2 (PB3)
CIC_RESET_N: TP7.1, U10.1 (~RESET/PB5)
CIC_RST: J1.70 (CIC +RST), U10.7 (PB2)
CIC_TOMB: J1.35 (CIC toMB), U10.5 (PB0)
CIC_TOPAK: J1.34 (CIC toPak), U10.6 (PB1)
CIRAM_A10: J1.22 (CIRAM A10); also elsewhere on the board
CIRAM_CE_N: J1.57 (CIRAM ~CE); also elsewhere on the board
CONS_5V: C31.1, J1.36 (+5V), U10.8 (VCC); also elsewhere on the board
GND: C31.2, J1.1 (GND), J1.72 (GND), U10.4 (GND); also elsewhere on the board
IRQ_N: J1.15 (~IRQ); also elsewhere on the board
M2: J1.38 (M2), TP5.1; also elsewhere on the board
PA0: J1.29 (PPU A0); also elsewhere on the board
PA1: J1.28 (PPU A1); also elsewhere on the board
PA2: J1.27 (PPU A2); also elsewhere on the board
PA3: J1.26 (PPU A3); also elsewhere on the board
PA4: J1.25 (PPU A4); also elsewhere on the board
PA5: J1.24 (PPU A5); also elsewhere on the board
PA6: J1.23 (PPU A6); also elsewhere on the board
PA7: J1.59 (PPU A7); also elsewhere on the board
PA8: J1.60 (PPU A8); also elsewhere on the board
PA9: J1.61 (PPU A9); also elsewhere on the board
PA10: J1.63 (PPU A10); also elsewhere on the board
PA11: J1.62 (PPU A11); also elsewhere on the board
PA12: J1.64 (PPU A12); also elsewhere on the board
PA13: J1.65 (PPU A13); also elsewhere on the board
PA13_N: J1.58 (PPU ~A13); also elsewhere on the board
PD0: J1.30 (PPU D0); also elsewhere on the board
PD1: J1.31 (PPU D1); also elsewhere on the board
PD2: J1.32 (PPU D2); also elsewhere on the board
PD3: J1.33 (PPU D3); also elsewhere on the board
PD4: J1.69 (PPU D4); also elsewhere on the board
PD5: J1.68 (PPU D5); also elsewhere on the board
PD6: J1.67 (PPU D6); also elsewhere on the board
PD7: J1.66 (PPU D7); also elsewhere on the board
PPU_RD_N: J1.21 (PPU ~RD); also elsewhere on the board
PPU_WR_N: J1.56 (PPU ~WR); also elsewhere on the board
ROMSEL_N: J1.50 (~ROMSEL); also elsewhere on the board
RW: J1.14 (CPU R/W); also elsewhere on the board

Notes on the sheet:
NES 72-pin edge drawn by function (finger numbers on the pins). Pin 1 is at the RIGHT seen from the label side with the fingers down (nesdev; NES-EWROM-01 geometry). EXP0-9 and SYSTEM CLK are not used. The CIClone (ATtiny13A) is DNP until its firmware exists.

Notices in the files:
NES/FujiNet-NES-Rev0/README.md:
Provenance and license:
CERN-OHL-W-2.0.** Circuit blocks adapted from `Astrocade/rev0` and
`INTV/FujiNet-INTV-Rev0` in this repository (themselves from the PiNTY
CARD, CERN-OHL-W-2.0) and the ESP32-S3-DevKitC-1 reference design, then
audited and changed as `docs/design-review-rev0.md` records. Edge pinout:
nesdev wiki *Cartridge connector*. Edge and outline geometry: nesdev *NES
cartridge dimensions* (NES-EWROM-01, Gumball2415's measurements, TAPR OHL --
dimensions only, no files copied), cross-checked against nesos-dev's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
